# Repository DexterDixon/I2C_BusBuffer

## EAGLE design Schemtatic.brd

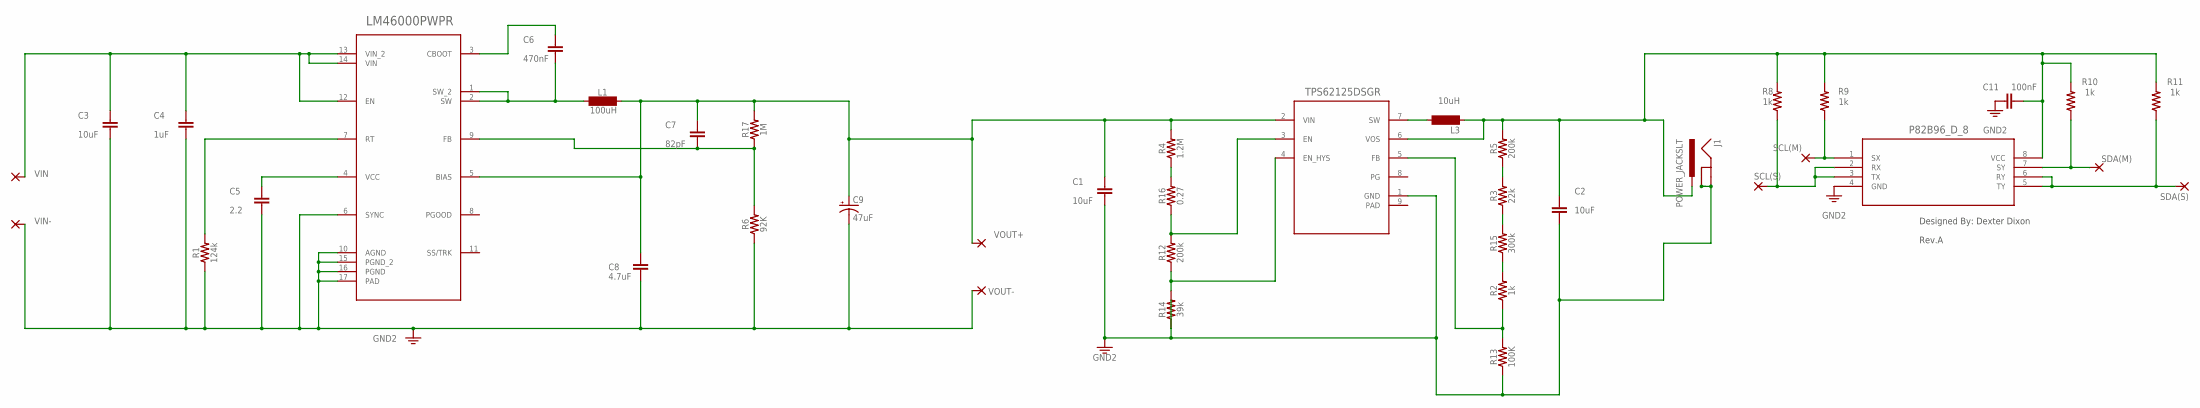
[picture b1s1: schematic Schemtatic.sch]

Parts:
C1, C2, C3: 10uF; C2.5-3
C4: 1uF; C2.5-3
C5: 2.2; C2.5-3
C6: 470nF; C2.5-3
C7: 82pF; C2.5-3
C8: 4.7uF; C2.5-3
C9: 47uF; EIA3528
C11: 100nF; C2.5-3
J1: POWER_JACKSLT; POWER_JACK_SLOT
L1: 100uH; MS42
L3: 10uH; MS42
R1: 124k; 0603
R2, R8, R9, R10, R11: 1k; 0603
R3: 22k; 0603
R4: 1.2M; 0603
R5, R12: 200k; 0603
R6: 92K; 0402
R13: 100K; 0402
R14: 39k; 0603
R15: 300k; 0603
R16: 0.27; 0603
R17: 1M; 0603
SCL(M): SMD5; SMD2,54-5,08
SCL(S): SMD5; SMD2,54-5,08
SDA(M): SMD5; SMD2,54-5,08
SDA(S): SMD5; SMD2,54-5,08
TPS62125DSGR: Value; DSG0008A
U1: LM46000PWPR; PWP0016F
U2: P82B96_D_8; D8
VIN+: SMD5; SMD2,54-5,08
VIN-: SMD5; SMD2,54-5,08
VOUT+: SMD5; SMD2,54-5,08
VOUT-: SMD5; SMD2,54-5,08

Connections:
3.3V: C1.2, C2.2, C3.2, C4.2, C5.2, C8.2, C9.C (-), C11.1, J1.GND@1 (GNDBREAK), J1.GND@2 (GND), R1.1, R6.1, R13.1, R14.1, TPS62125DSGR.1 (GND), U1.6 (SYNC), U1.10 (AGND), U1.15 (PGND_2), U1.16 (PGND), U1.17 (PAD), U2.4 (GND), VIN-.1, VOUT-.1
unnamed: R8.1, SCL(S).1, U2.2 (RX), U2.3 (TX)
unnamed: R11.1, SDA(S).1, U2.5 (TY), U2.6 (RY)
unnamed: L3.2, TPS62125DSGR.7 (SW)
unnamed: R12.1, R14.2, TPS62125DSGR.4 (EN_HYS)
unnamed: R12.2, R16.1, TPS62125DSGR.3 (EN)
unnamed: C2.1, C11.2, J1.PWR, L3.1, R5.2, R8.2, R9.2, R10.2, R11.2, TPS62125DSGR.6 (VOS), U2.8 (VCC)
unnamed: C5.1, U1.4 (VCC)
unnamed: R3.2, R5.1
unnamed: R4.1, R16.2
unnamed: R9.1, SCL(M).1, U2.1 (SX)
unnamed: R10.1, SDA(M).1, U2.7 (SY)
unnamed: C6.2, L1.2, U1.1 (SW_2), U1.2 (SW)
unnamed: C6.1, U1.3 (CBOOT)
unnamed: C7.2, R6.2, R17.1, U1.9 (FB)
unnamed: R2.1, R13.2, TPS62125DSGR.5 (FB)
unnamed: C1.1, C7.1, C8.1, C9.A (+), L1.1, R4.2, R17.2, TPS62125DSGR.2 (VIN), U1.5 (BIAS), VOUT+.1
unnamed: R3.1, R15.2
unnamed: R2.2, R15.1
unnamed: R1.2, U1.7 (RT)
PAD: TPS62125DSGR.9 (PAD)
VIN+: C3.1, C4.1, U1.12 (EN), U1.13 (VIN_2), U1.14 (VIN), VIN+.1

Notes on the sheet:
Designed By: Dexter Dixon
Rev.A

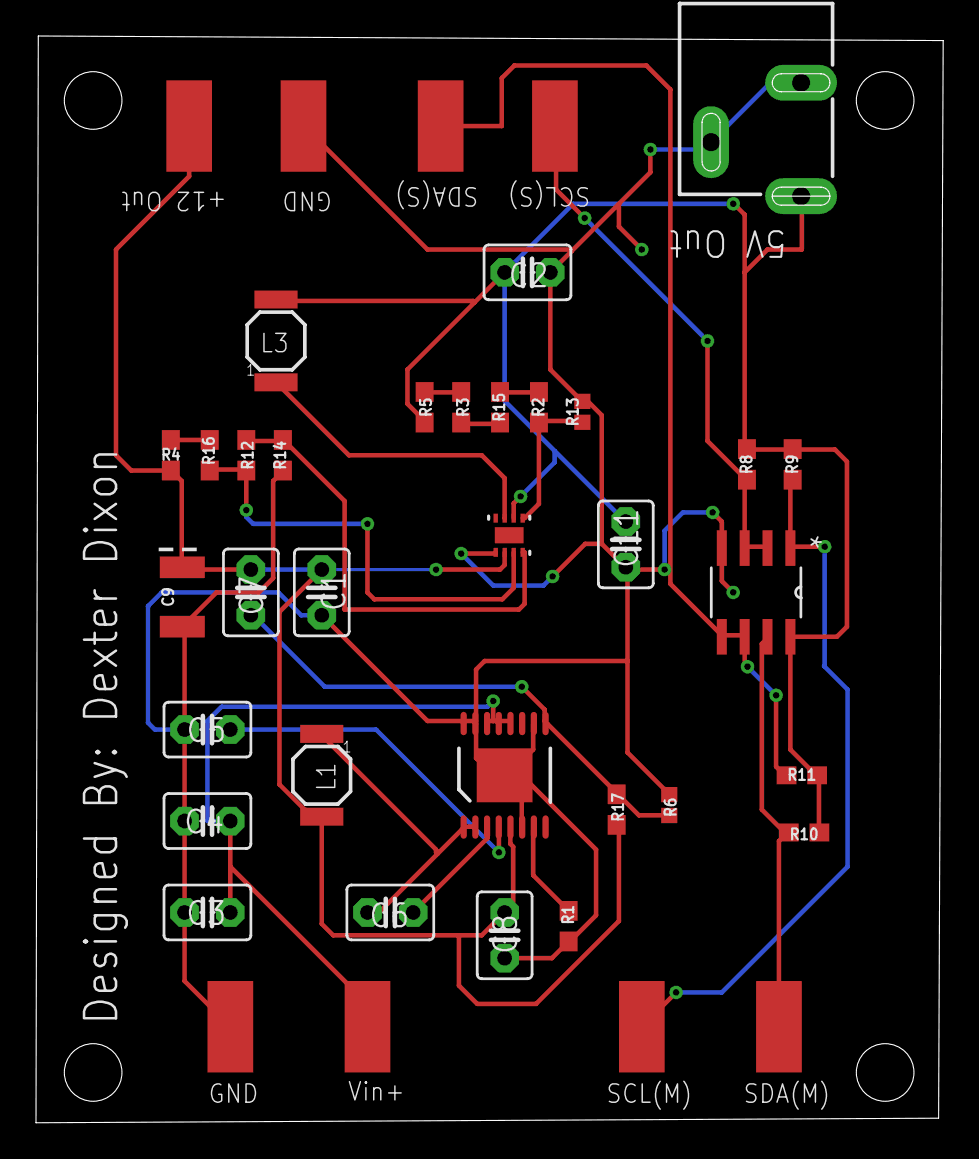
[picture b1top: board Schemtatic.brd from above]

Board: 2 copper layers, 50.4 x 60.4 mm, 40 parts (0 on the bottom side), 21 nets.

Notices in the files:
parts and their libraries:
SparkFun-Capacitors: Licensing: Creative Commons ShareAlike 4.0 International - https://creativecommons.org/licenses/by-sa/4.0
